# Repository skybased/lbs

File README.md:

# Lets-Build-Something
An arduino Uno sketch with Foutx4, I/Q and making use of 2.2"TFT Display

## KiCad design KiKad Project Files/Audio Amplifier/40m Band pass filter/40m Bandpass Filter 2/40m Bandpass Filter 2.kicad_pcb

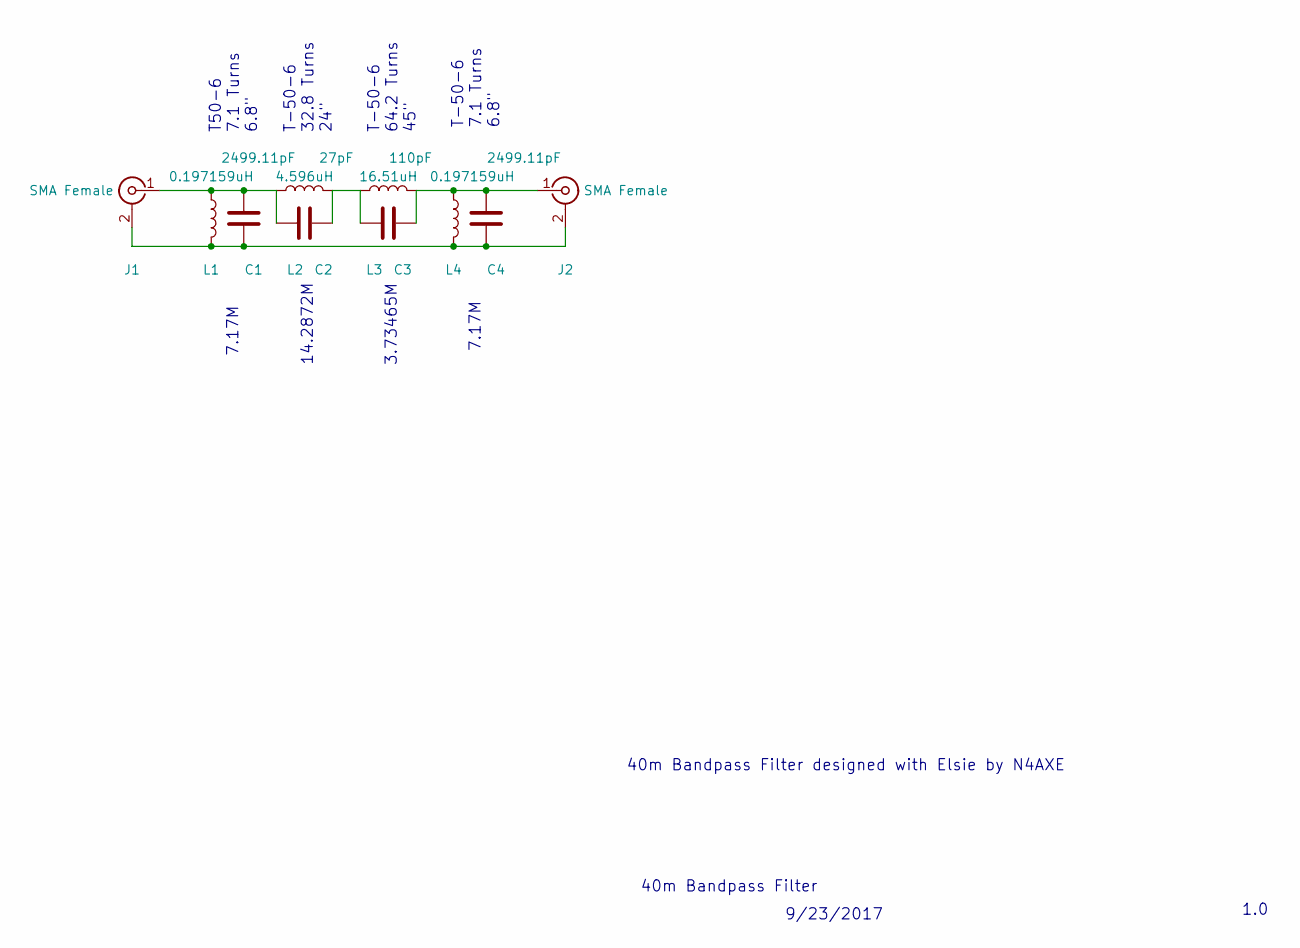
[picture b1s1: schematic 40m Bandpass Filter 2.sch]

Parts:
C1, C4: 2499.11pF; C_Rect_L11.5mm_W6.4mm_P10.00mm_MKT
C2: 27pF; C_Rect_L11.5mm_W6.4mm_P10.00mm_MKT
C3: 110pF; C_Rect_L11.5mm_W6.4mm_P10.00mm_MKT
J1, J2: SMA Female; SMA_THT_Jack_Straight
L1, L4: 0.197159uH; L_Toroid_Vertical_L10.0mm_W5.0mm_P5.08mm
L2: 4.596uH; L_Toroid_Vertical_L10.0mm_W5.0mm_P5.08mm
L3: 16.51uH; L_Toroid_Vertical_L10.0mm_W5.0mm_P5.08mm

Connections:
unnamed: C1.1, C2.2, J1.1 (In), L1.1, L2.1
unnamed: C1.2, C4.2, J1.2 (Ext), J2.2 (Ext), L1.2, L4.2
unnamed: C2.1, C3.2, L2.2, L3.1
unnamed: C3.1, C4.1, J2.1 (In), L3.2, L4.1

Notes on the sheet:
40m Bandpass Filter
9/23/2017
1.0
7.17M
14.2872M
3.73465M
T50-6 7.1 Turns 6.8"
T-50-6 32.8 Turns 24"
T-50-6 7.1 Turns 6.8"
T-50-6 64.2 Turns 45"
40m Bandpass Filter designed with Elsie by N4AXE

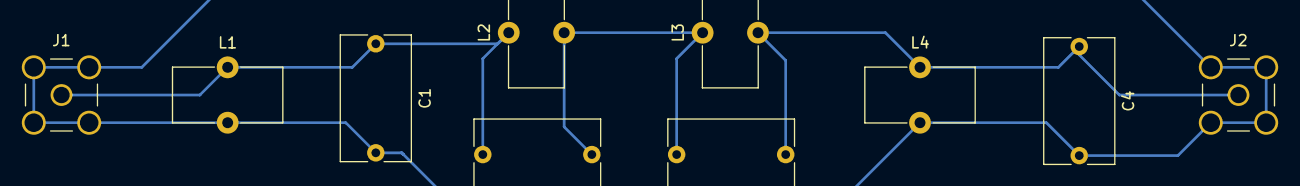
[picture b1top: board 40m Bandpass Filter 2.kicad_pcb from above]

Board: 2 copper layers, 10 parts (0 on the bottom side), 4 nets.

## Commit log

2017-11-13 Arduino Sketch For Lets Build Something Radio
    Five band ready
    si5351 x4 out for use with /4 flipflop 6-12db gain in dynamic range
    2.2" TFT Display Required CD 4050 Level Shifter
    USB/LSB
    Tune Function with 988hz tone with proper LO output
    Added further comments to variables
2017-11-13 Added PDF and Kikad & Pete's Original Schematics
    Missing a few need to clean up a few things, will add them asap
2017-11-13 Other Files
    Some Data Sheets and Misc info
2017-11-15 All the required libraries
